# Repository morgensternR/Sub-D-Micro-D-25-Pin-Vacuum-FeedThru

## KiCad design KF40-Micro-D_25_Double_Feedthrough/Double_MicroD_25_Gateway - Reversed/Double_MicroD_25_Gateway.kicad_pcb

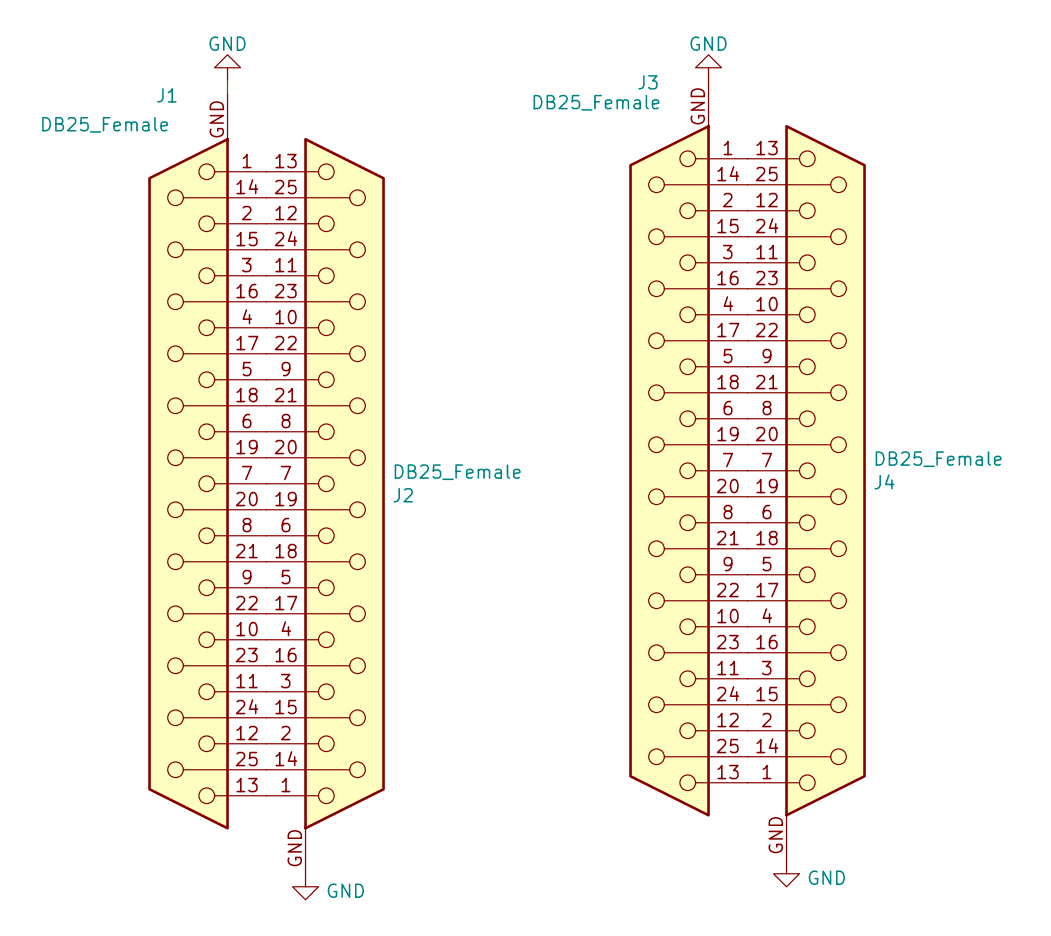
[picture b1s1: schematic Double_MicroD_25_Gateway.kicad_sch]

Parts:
J1, J2, J3, J4: DB25_Female; Norcomp-380-025-113L001-microd_Updated

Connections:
GND: J1.GND, J2.GND, J3.GND, J4.GND
unnamed: J1.1, J2.13
unnamed: J1.2, J2.12
unnamed: J1.3, J2.11
unnamed: J1.4, J2.10
unnamed: J1.5, J2.9
unnamed: J1.6, J2.8
unnamed: J1.7, J2.7
unnamed: J1.8, J2.6
unnamed: J1.9, J2.5
unnamed: J1.10, J2.4
unnamed: J1.11, J2.3
unnamed: J1.12, J2.2
unnamed: J1.13, J2.1
unnamed: J1.14, J2.25
unnamed: J1.15, J2.24
unnamed: J1.16, J2.23
unnamed: J1.17, J2.22
unnamed: J1.18, J2.21
unnamed: J1.19, J2.20
unnamed: J1.20, J2.19
unnamed: J1.21, J2.18
unnamed: J1.22, J2.17
unnamed: J1.23, J2.16
unnamed: J1.24, J2.15
unnamed: J1.25, J2.14
unnamed: J3.1, J4.13
unnamed: J3.2, J4.12
unnamed: J3.3, J4.11
unnamed: J3.4, J4.10
unnamed: J3.5, J4.9
unnamed: J3.6, J4.8
unnamed: J3.7, J4.7
unnamed: J3.8, J4.6
unnamed: J3.9, J4.5
unnamed: J3.10, J4.4
unnamed: J3.11, J4.3
unnamed: J3.12, J4.2
unnamed: J3.13, J4.1
unnamed: J3.14, J4.25
unnamed: J3.15, J4.24
unnamed: J3.16, J4.23
unnamed: J3.17, J4.22
unnamed: J3.18, J4.21
unnamed: J3.19, J4.20
unnamed: J3.20, J4.19
unnamed: J3.21, J4.18
unnamed: J3.22, J4.17
unnamed: J3.23, J4.16
unnamed: J3.24, J4.15
unnamed: J3.25, J4.14

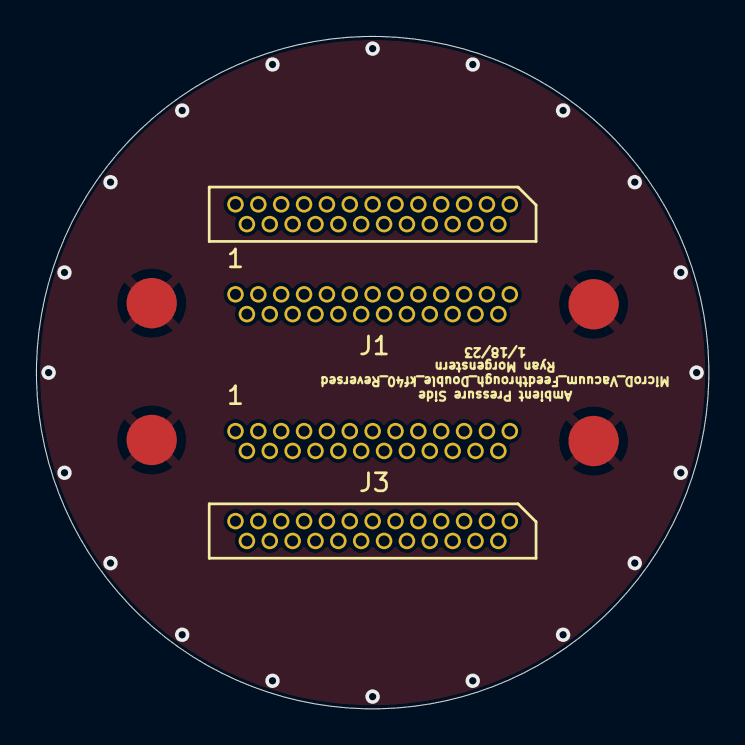
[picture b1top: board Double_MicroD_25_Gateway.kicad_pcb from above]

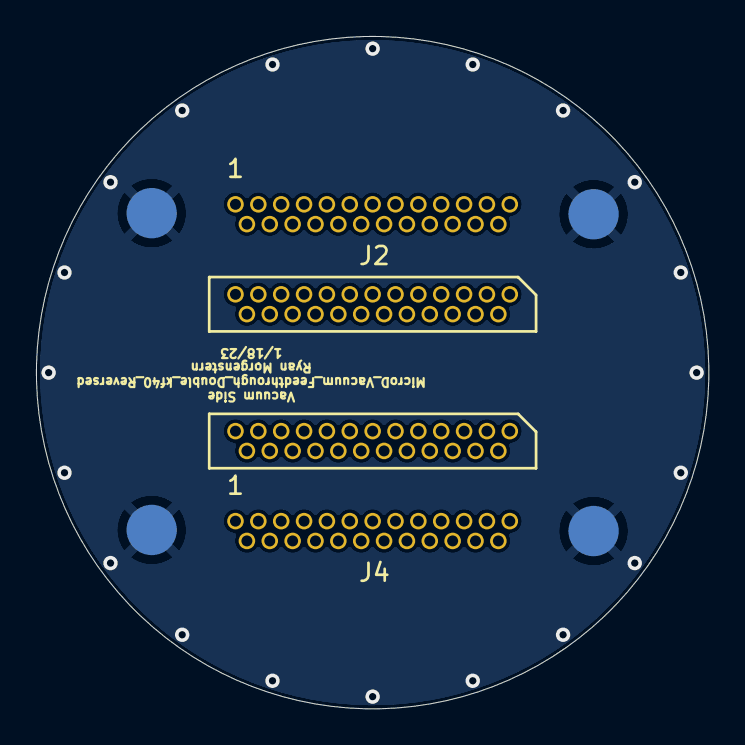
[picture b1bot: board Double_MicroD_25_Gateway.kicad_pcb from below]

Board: 4 copper layers, 37.4 x 37.4 mm, 4 parts (2 on the bottom side), 51 nets.

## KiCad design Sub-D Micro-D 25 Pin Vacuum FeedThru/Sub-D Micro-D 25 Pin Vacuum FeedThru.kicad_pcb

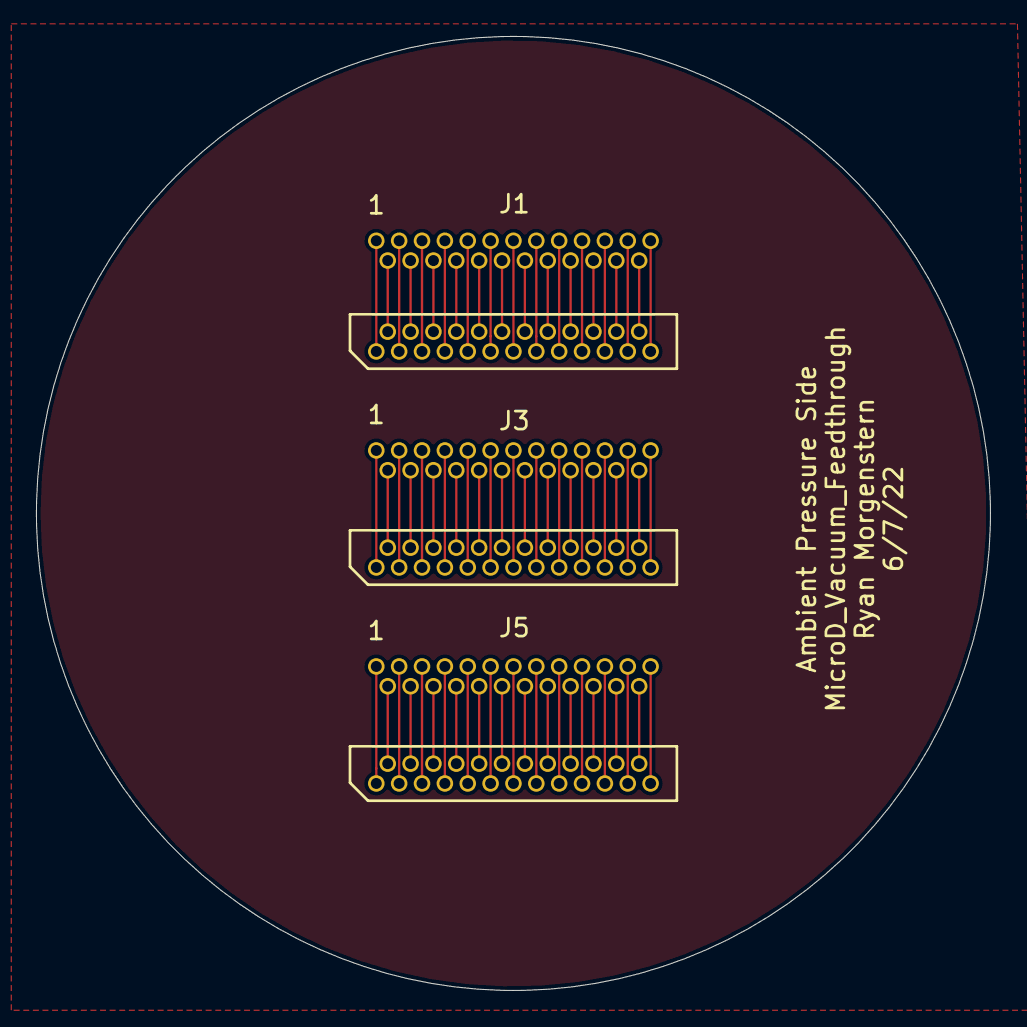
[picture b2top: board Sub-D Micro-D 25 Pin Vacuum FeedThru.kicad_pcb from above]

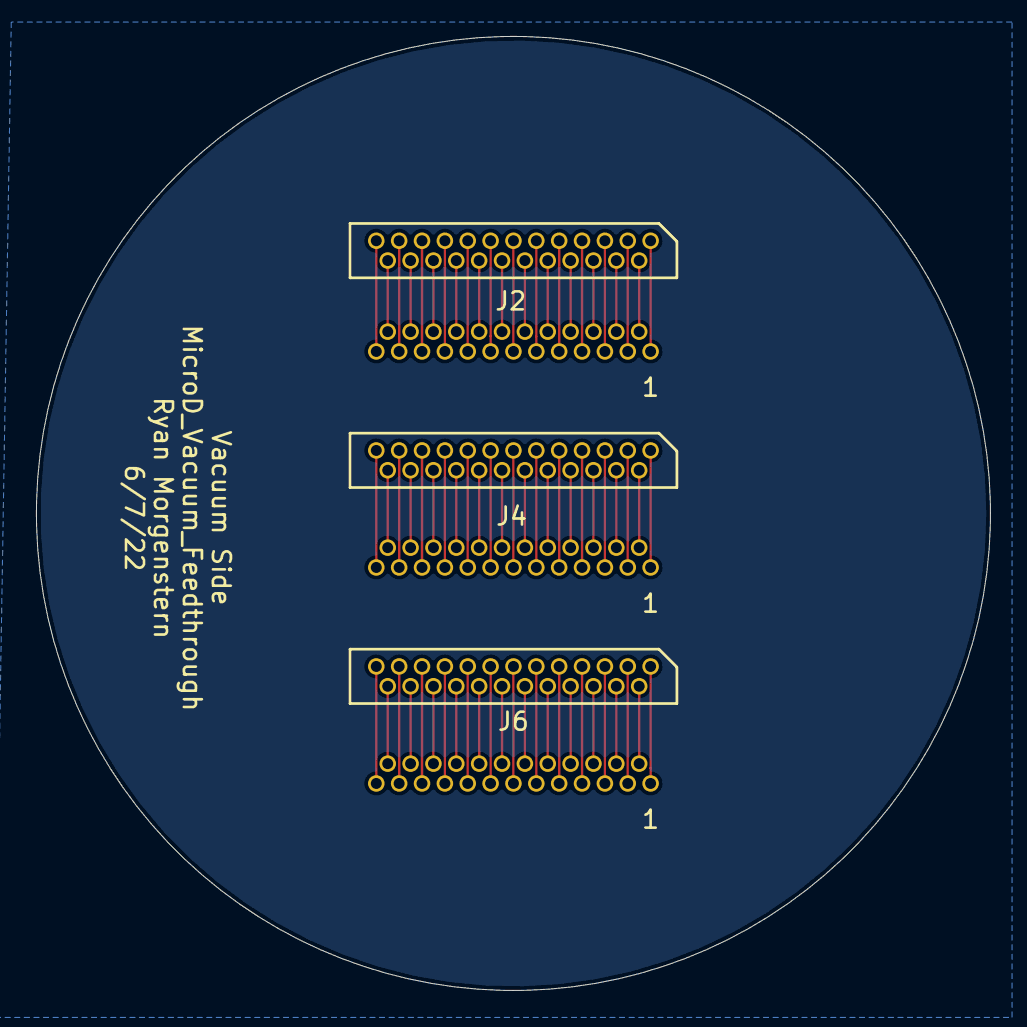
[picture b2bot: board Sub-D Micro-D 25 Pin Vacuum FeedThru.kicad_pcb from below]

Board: 4 copper layers, 53.0 x 53.0 mm, 6 parts (3 on the bottom side), 75 nets.

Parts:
J1, J2, J3, J4, J5, J6: DB25_Male; Norcomp-380-025-113L001-microd_Updated

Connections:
unnamed: J1.1, J2.1
unnamed: J1.2, J2.2
unnamed: J1.3, J2.3
unnamed: J1.4, J2.4
unnamed: J1.5, J2.5
unnamed: J1.6, J2.6
unnamed: J1.7, J2.7
unnamed: J1.8, J2.8
unnamed: J1.9, J2.9
unnamed: J1.10, J2.10
unnamed: J1.11, J2.11
unnamed: J1.12, J2.12
unnamed: J1.13, J2.13
unnamed: J1.14, J2.14
unnamed: J1.15, J2.15
unnamed: J1.16, J2.16
unnamed: J1.17, J2.17
unnamed: J1.18, J2.18
unnamed: J1.19, J2.19
unnamed: J1.20, J2.20
unnamed: J1.21, J2.21
unnamed: J1.22, J2.22
unnamed: J1.23, J2.23
unnamed: J1.24, J2.24
unnamed: J1.25, J2.25
unnamed: J3.1, J4.1
unnamed: J3.2, J4.2
unnamed: J3.3, J4.3
unnamed: J3.4, J4.4
unnamed: J3.5, J4.5
unnamed: J3.6, J4.6
unnamed: J3.7, J4.7
unnamed: J3.8, J4.8
unnamed: J3.9, J4.9
unnamed: J3.10, J4.10
unnamed: J3.11, J4.11
unnamed: J3.12, J4.12
unnamed: J3.13, J4.13
unnamed: J3.14, J4.14
unnamed: J3.15, J4.15
unnamed: J3.16, J4.16
unnamed: J3.17, J4.17
unnamed: J3.18, J4.18
unnamed: J3.19, J4.19
unnamed: J3.20, J4.20
unnamed: J3.21, J4.21
unnamed: J3.22, J4.22
unnamed: J3.23, J4.23
unnamed: J3.24, J4.24
unnamed: J3.25, J4.25
unnamed: J5.1, J6.1
unnamed: J5.2, J6.2
unnamed: J5.3, J6.3
unnamed: J5.4, J6.4
unnamed: J5.5, J6.5
unnamed: J5.6, J6.6
unnamed: J5.7, J6.7
unnamed: J5.8, J6.8
unnamed: J5.9, J6.9
unnamed: J5.10, J6.10
unnamed: J5.11, J6.11
unnamed: J5.12, J6.12
unnamed: J5.13, J6.13
unnamed: J5.14, J6.14
unnamed: J5.15, J6.15
unnamed: J5.16, J6.16
unnamed: J5.17, J6.17
unnamed: J5.18, J6.18
unnamed: J5.19, J6.19
unnamed: J5.20, J6.20
unnamed: J5.21, J6.21
unnamed: J5.22, J6.22
unnamed: J5.23, J6.23
unnamed: J5.24, J6.24
unnamed: J5.25, J6.25

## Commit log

2021-07-01 Initial
2021-07-21 Update Gerber
2021-07-21 Gerber Update
2021-07-22 Cu Update
2023-01-18 updated kf40- reversed
